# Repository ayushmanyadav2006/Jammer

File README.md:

# Jammer
2.4Ghz Bluetooth and WIFI jammer
Jams 2.4 Ghz frequency band by transmitting garbage data randomly by ignoring the proper method of transmitting the data, because of this disturbance is caused on the 2.4Ghz band and all the devices which are connected in the 2.4Ghz band gets affected. 

Working video link: https://www.youtube.com/watch?v=O3qsxE17gZQ

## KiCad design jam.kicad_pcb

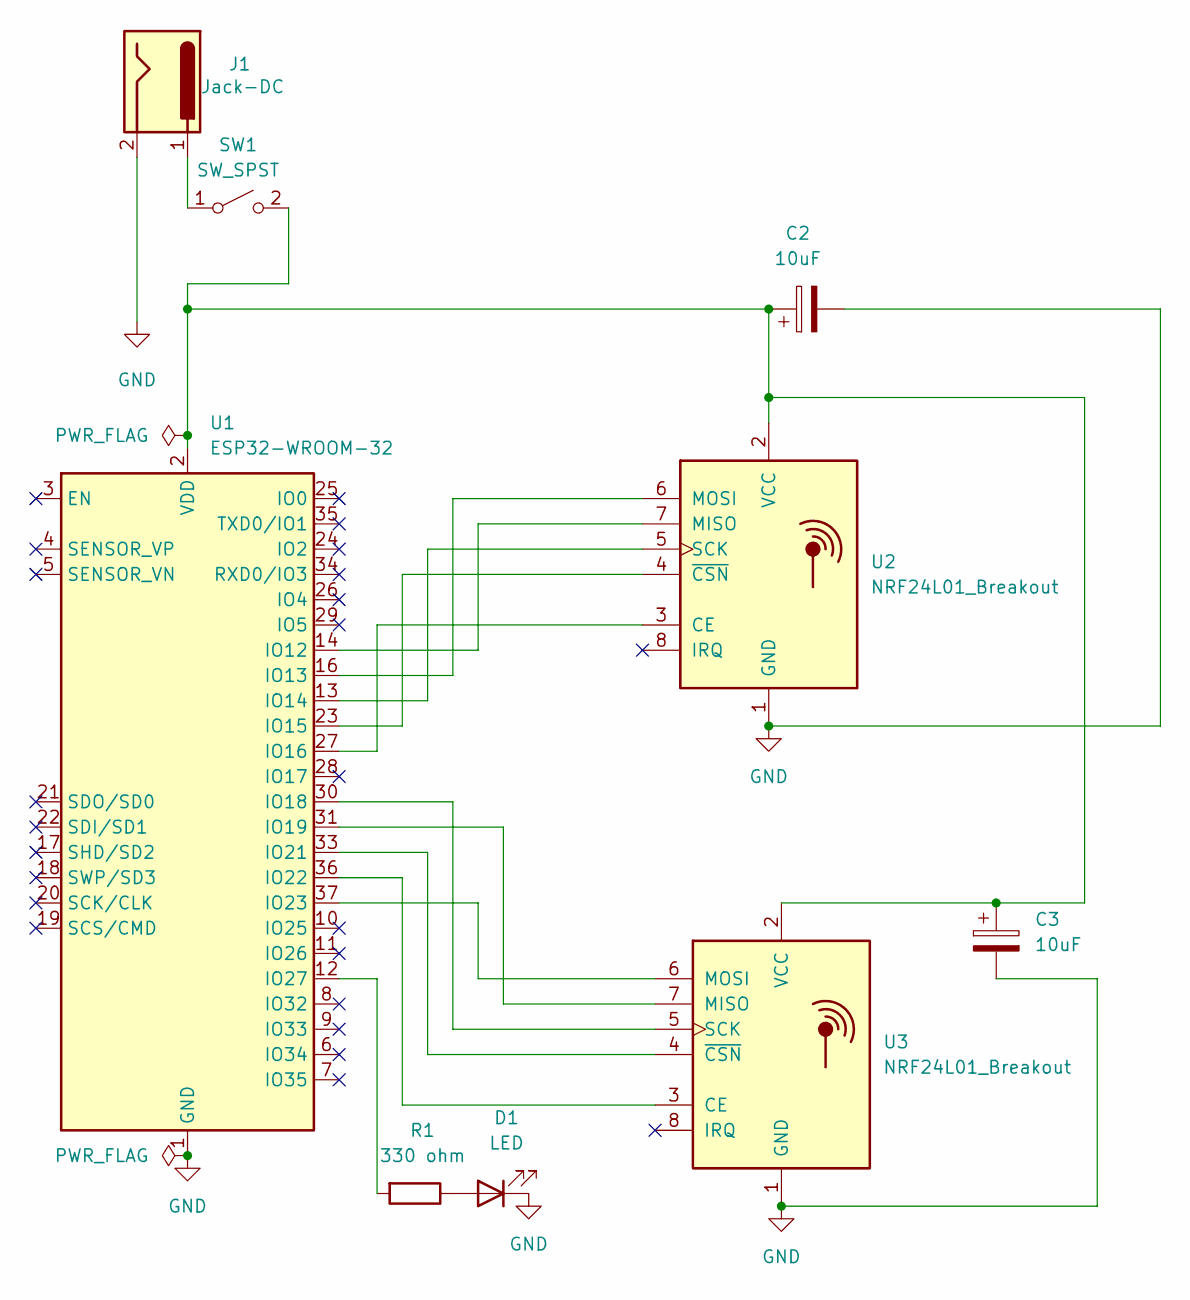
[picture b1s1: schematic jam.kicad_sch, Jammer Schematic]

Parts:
C2, C3: 10uF; CP_Axial_L10.0mm_D4.5mm_P15.00mm_Horizontal
D1: LED; LED_D3.0mm
J1: Jack-DC; BarrelJack_Horizontal
R1: 330 ohm; R_Axial_DIN0204_L3.6mm_D1.6mm_P5.08mm_Horizontal
SW1: SW_SPST; KSA_Tactile_SPST
U1: ESP32-WROOM-32
U2, U3: NRF24L01_Breakout; nRF24L01_Breakout

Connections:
GND: C2.2, C3.2, D1.1 (K), J1.2, U1.1 (GND), U1.15 (GND), U1.38 (GND), U1.39 (GND), U2.1 (GND), U3.1 (GND)
unnamed: D1.2 (A), R1.1
unnamed: J1.1, SW1.1 (A)
unnamed: C2.1, C3.1, SW1.2 (B), U1.2 (VDD), U2.2 (VCC), U3.2 (VCC)
unnamed: U1.14 (IO12), U2.7 (MISO)
unnamed: U1.16 (IO13), U2.6 (MOSI)
unnamed: U1.13 (IO14), U2.5 (SCK)
unnamed: U1.23 (IO15), U2.4 (~CSN)
unnamed: U1.27 (IO16), U2.3 (CE)
unnamed: U1.30 (IO18), U3.5 (SCK)
unnamed: U1.31 (IO19), U3.7 (MISO)
unnamed: U1.33 (IO21), U3.4 (~CSN)
unnamed: U1.36 (IO22), U3.3 (CE)
unnamed: U1.37 (IO23), U3.6 (MOSI)
unnamed: R1.2, U1.12 (IO27)

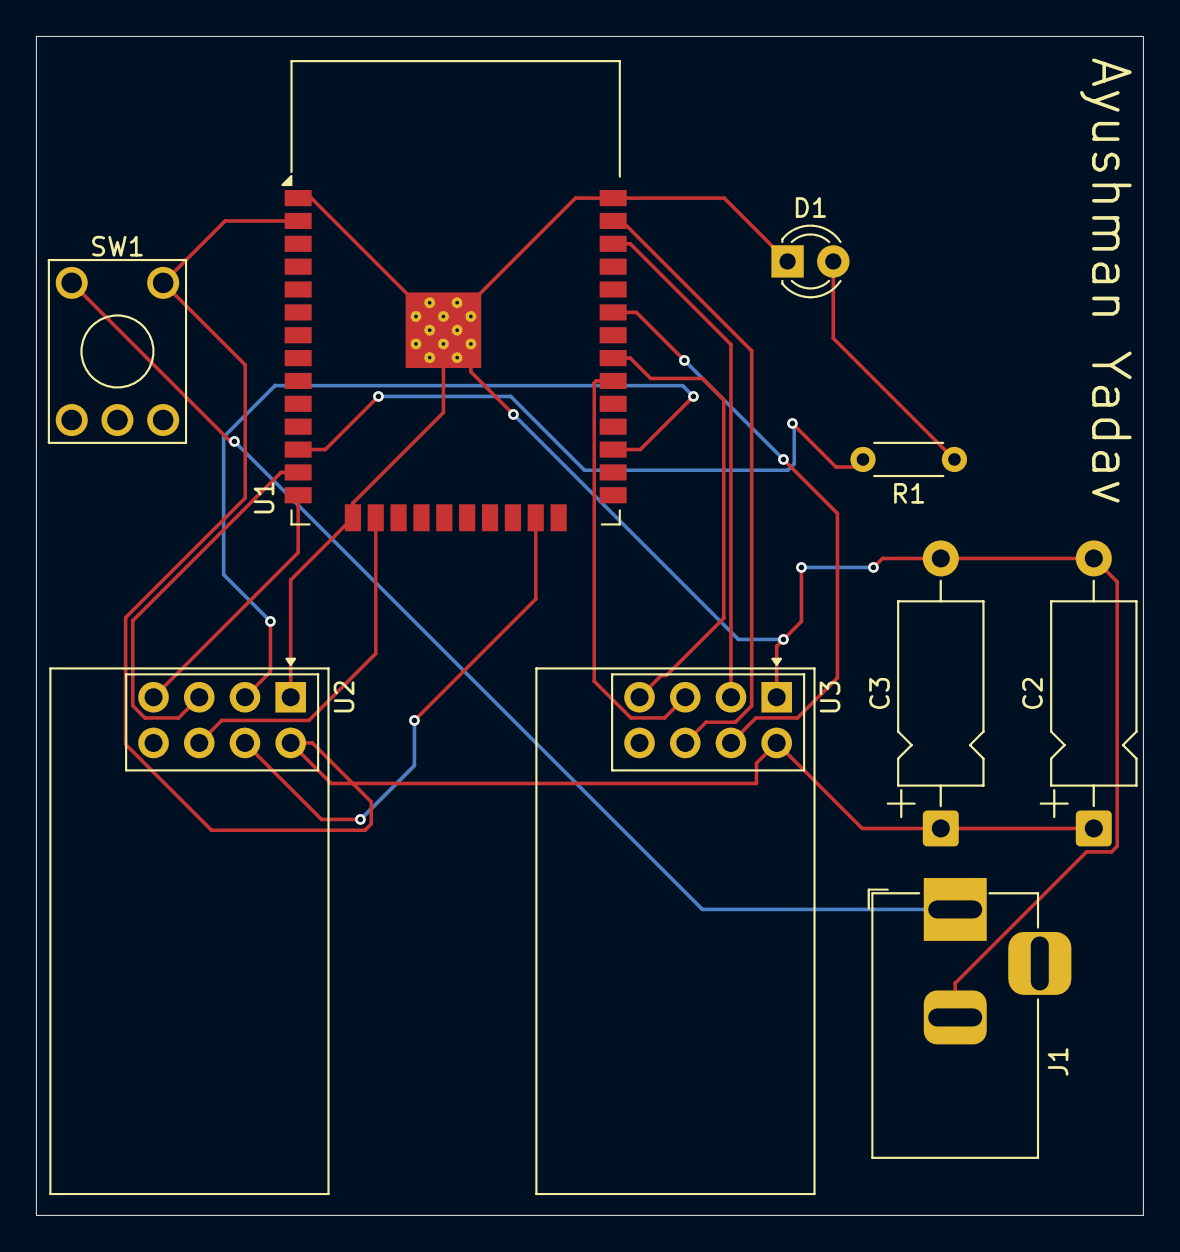
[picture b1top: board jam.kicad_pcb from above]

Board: 2 copper layers, 61.5 x 65.5 mm, 9 parts (0 on the bottom side), 15 nets.

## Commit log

2026-06-30 Enhance README with detailed jammer functionality
    Added explanation of how the jammer operates.
